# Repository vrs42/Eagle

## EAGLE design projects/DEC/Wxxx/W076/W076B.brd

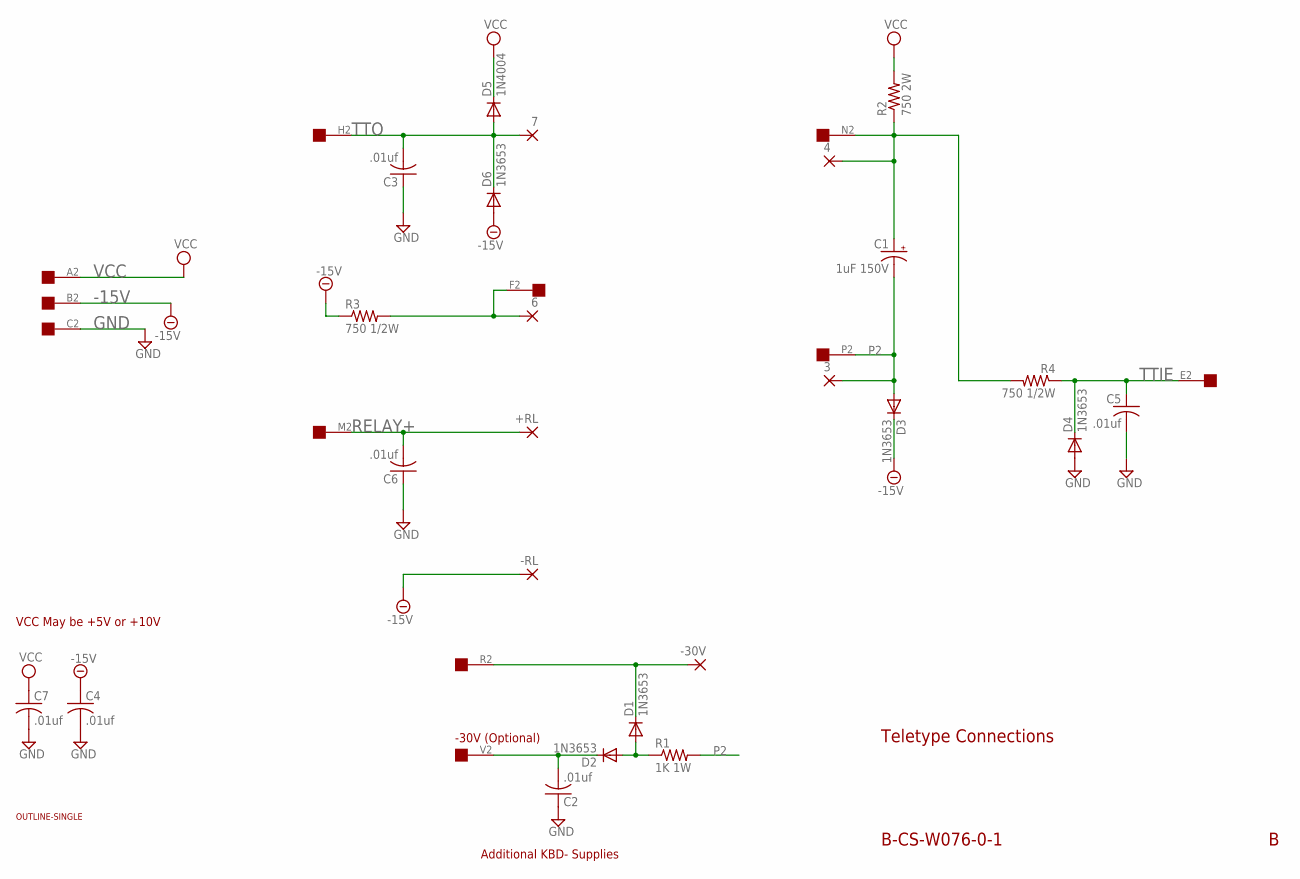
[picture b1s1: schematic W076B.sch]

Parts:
3, 4, 6, 7: 2,54/1,0
+RL: 2,54/1,0
-30V: 2,54/1,0
-RL: 2,54/1,0
C1: 1uF 150V; E25-9
C2, C3, C4, C5, C6, C7: .01uf; C050-025X075
D1, D2, D3, D4, D6: 1N3653; DO35-10
D5: 1N4004; DO35-10
EDGE: EDGE-1; EDGE-CON1
R1: 1K 1W; 0617/22
R2: 750 2W; P0817/22
R3, R4: 750 1/2W; 0411/15
U$1: OUTLINE-SINGLE; SINGLE

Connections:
-15V: -RL.1, C4.1, D3.C, D6.A, EDGE.B2, R3.1
GND: C2.1, C3.1, C4.2, C5.2, C6.1, C7.2, D4.A, EDGE.C2
unnamed: 6.1, EDGE.F2, R3.2
unnamed: -30V.1, D1.C, EDGE.R2
unnamed: C2.2, D2.C, EDGE.V2
unnamed: D1.A, D2.A, R1.1
unnamed: 4.1, C1.+, EDGE.N2, R2.1, R4.2
P2: 3.1, C1.-, D3.A, EDGE.P2, R1.2
RELAY+: +RL.1, C6.2, EDGE.M2
TTIE: C5.1, D4.C, EDGE.E2, R4.1
TTO: 7.1, C3.2, D5.A, D6.C, EDGE.H2
VCC: C7.1, D5.C, EDGE.A2, R2.2

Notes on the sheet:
Teletype Connections
VCC May be +5V or +10V
Additional KBD- Supplies
-30V (Optional)
B-CS-W076-0-1

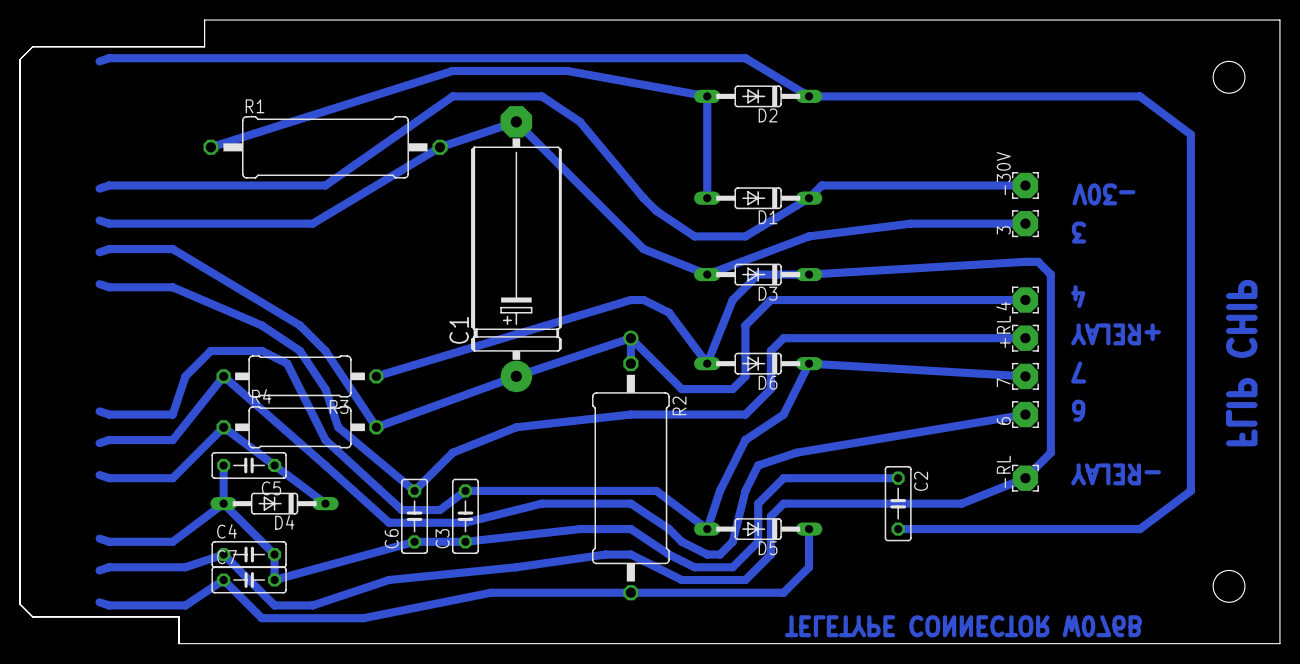
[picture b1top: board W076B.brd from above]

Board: 2 copper layers, 125.7 x 62.2 mm, 27 parts (1 on the bottom side), 12 nets.

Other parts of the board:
U$2: FLIPCHIP

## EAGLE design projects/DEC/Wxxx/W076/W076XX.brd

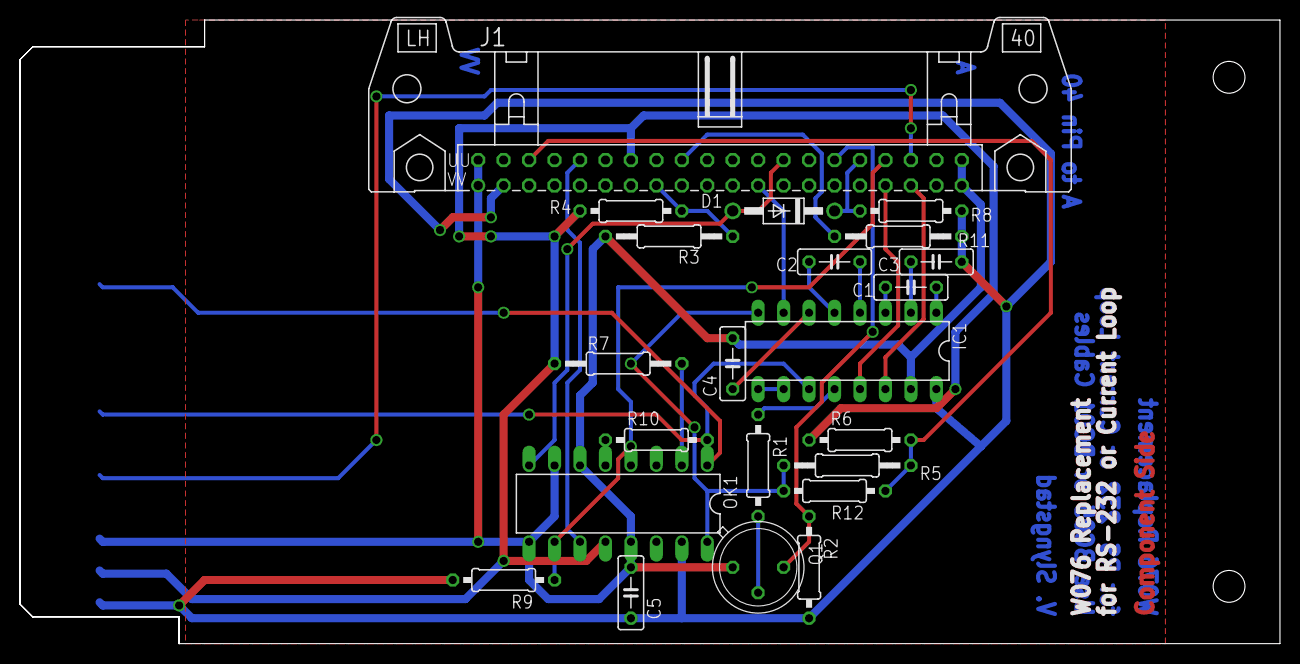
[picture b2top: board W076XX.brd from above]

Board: 2 copper layers, 125.7 x 62.2 mm, 24 parts (0 on the bottom side), 29 nets.

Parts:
C1, C2, C3, C4, C5: .1uf; C050-025X075
D1: 1N914; DO41-10
IC1: MAX232A; DIL16
J1: DEC40PINSH; DEC40PINH
OK1: LTV845; DIL16
Q1: PN2222; TO5
R1: 470; 0207/10
R2, R6, R9, R12: 5.1K; 0207/10
R3, R5, R7: 680 1/2W; 0207/12
R4, R8, R10: 220; 0207/10
R11: 1K 1/2W; 0207/12
U$2: EDGE-1; EDGE-CON1
U$3: OUTLINE-SINGLE; SINGLE

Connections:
20MA-INTERLOCK: J1.H, OK1.10, R9.1
+20MA: D1.C, J1.K, R8.1
-15V: J1.EE, OK1.12, R4.2, R6.1, R7.1, U$2.B2
-20MA: D1.A, J1.S, OK1.8
DTR-EIA: J1.DD, R3.1, R4.1
EIA-INTERLOCK: J1.M, Q1.3, R2.1
GND: C4.2, C5.1, IC1.15, J1.A, J1.B, J1.UU, J1.VV, OK1.6, OK1.7, OK1.9, OK1.13, Q1.1, R3.2, U$2.C2
unnamed: C2.1, IC1.5
unnamed: C2.2, IC1.4
unnamed: C1.2, IC1.1
unnamed: C1.1, IC1.3
unnamed: OK1.2, R7.2
unnamed: IC1.9, IC1.10
unnamed: IC1.8, OK1.16, R5.2, R12.2
unnamed: IC1.12, R1.1
unnamed: C3.2, IC1.2
unnamed: C4.1, IC1.6
unnamed: Q1.2, R1.2
unnamed: OK1.5, R10.1
RDR-RUN: OK1.1, U$2.M2
RELAY+: J1.PP, R5.1, R6.2, R12.1
RTS-EIA: IC1.7, J1.V
RX-DATA: J1.E, U$2.E2
RX-EIA: IC1.13, J1.J
TX+: J1.AA, R11.2
TX-: J1.KK, OK1.11
TX-DATA: IC1.11, R10.2, U$2.H2
TX-EIA: IC1.14, J1.F
VCC: C3.1, C5.2, IC1.16, J1.TT, OK1.15, R2.2, R8.2, R9.2, R11.1, U$2.A2

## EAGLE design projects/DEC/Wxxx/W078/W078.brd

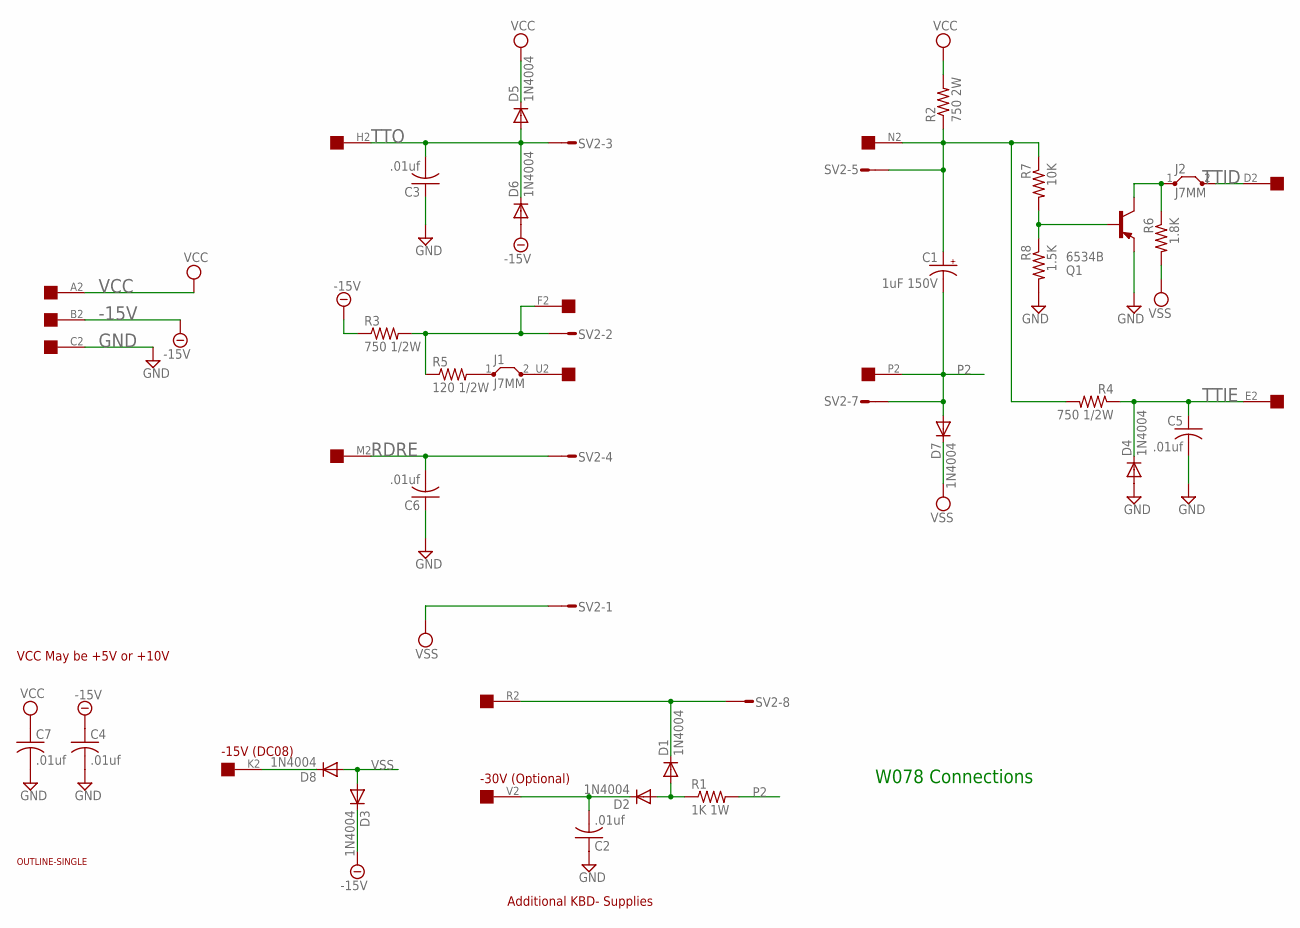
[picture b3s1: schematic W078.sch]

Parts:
C1: 1uF 150V; E22-6
C2, C3, C4, C5, C6, C7: .01uf; C050-025X075
D1, D2, D3, D4, D5, D6, D7, D8: 1N4004; DO35-10
EDGE: EDGE-1; EDGE-CON1
J1, J2: J7MM; 07
Q1: 6534B; TO92/
R1: 1K 1W; 0411/15
R2: 750 2W; 0411/15
R3, R4: 750 1/2W; 0309/12
R5: 120 1/2W; 0309/12
R6: 1.8K; 0207/10
R7: 10K; 0207/10
R8: 1.5K; 0207/10
SV2: L08P
U$1: OUTLINE-SINGLE; SINGLE

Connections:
-15V: C4.1, D3.C, D6.A, EDGE.B2, R3.1
GND: C2.1, C3.1, C4.2, C5.2, C6.1, C7.2, D4.A, EDGE.C2, Q1.1 (E), R8.2
unnamed: EDGE.F2, R3.2, R5.1, SV2.2
unnamed: Q1.2 (B), R7.2, R8.1
unnamed: D1.C, EDGE.R2, SV2.8
unnamed: D8.C, EDGE.K2
unnamed: C2.2, D2.C, EDGE.V2
unnamed: D1.A, D2.A, R1.1
unnamed: C1.+, EDGE.N2, R2.1, R4.2, R7.1, SV2.5
unnamed: J1.1, R5.2
unnamed: J2.1, Q1.3 (C), R6.1
P2: C1.-, D7.A, EDGE.P2, R1.2, SV2.7
RDRE: C6.2, EDGE.M2, SV2.4
TTID: EDGE.D2, J2.2
TTIE: C5.1, D4.C, EDGE.E2, R4.1
TTO: C3.2, D5.A, D6.C, EDGE.H2, SV2.3
TTOE: EDGE.U2, J1.2
VCC: C7.1, D5.C, EDGE.A2, R2.2
VSS: D3.A, D7.C, D8.A, R6.2, SV2.1

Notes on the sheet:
W078 Connections
VCC May be +5V or +10V
Additional KBD- Supplies
-30V (Optional)
-15V (DC08)

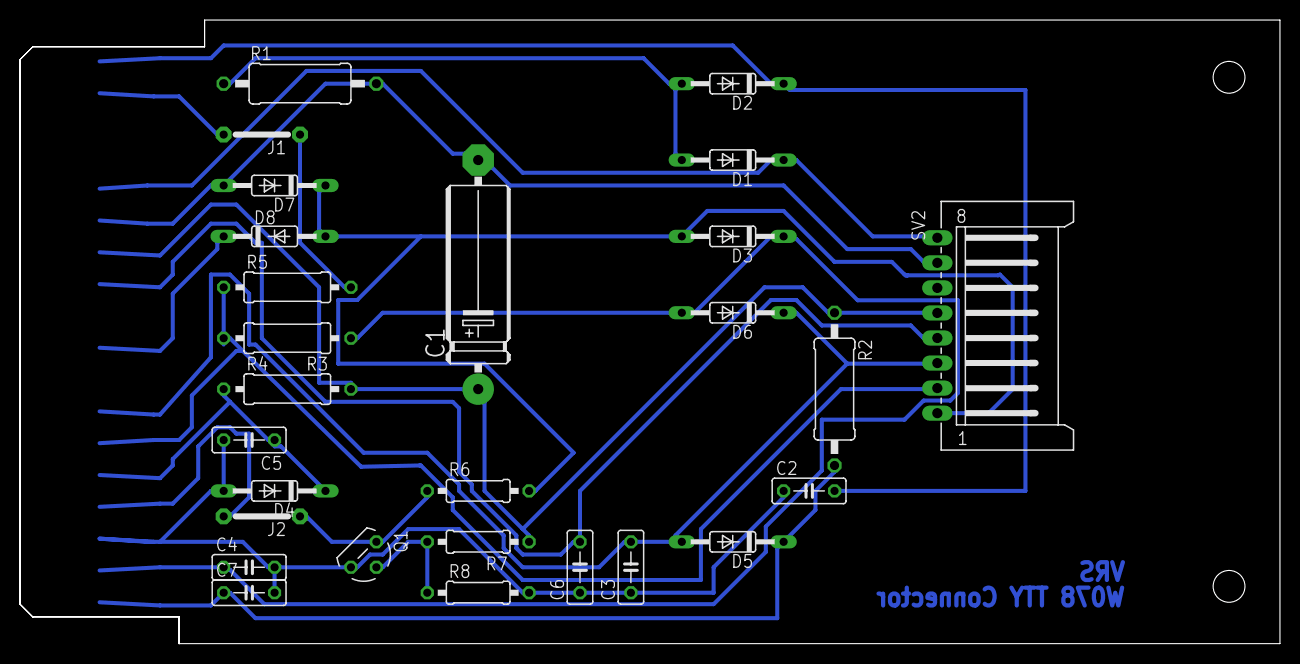
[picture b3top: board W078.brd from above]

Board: 2 copper layers, 125.7 x 62.2 mm, 29 parts (0 on the bottom side), 19 nets.

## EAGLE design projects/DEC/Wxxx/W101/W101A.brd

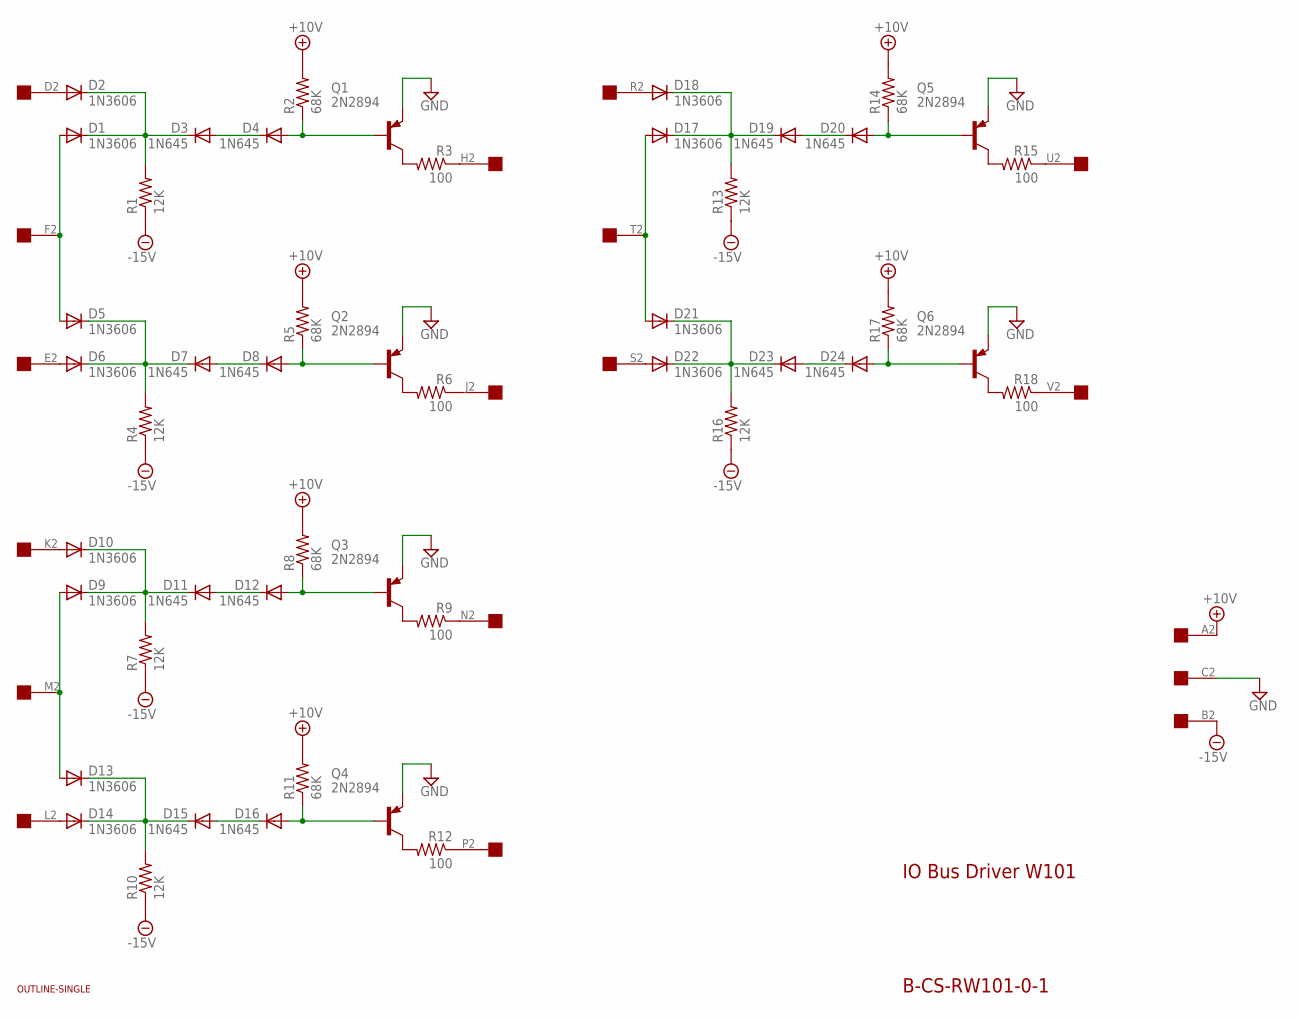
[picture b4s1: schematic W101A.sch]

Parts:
D1, D2, D5, D6, D9, D10, D13, D14, D17, D18, D21, D22: 1N3606; DO35-10
D3, D4, D7, D8, D11, D12, D15, D16, D19, D20, D23, D24: 1N645; DO35-10
Q1, Q2, Q3, Q4, Q5, Q6: 2N2894; TO39
R1, R4, R7, R10, R13, R16: 12K; 0207/10
R2, R5, R8, R11, R14, R17: 68K; 0207/10
R3, R6, R9, R12, R15, R18: 100; 0207/10
U$1: OUTLINE-SINGLE; SINGLE
U$2: EDGE-1; EDGE-CON1

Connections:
+10V: R2.2, R5.2, R8.2, R11.2, R14.2, R17.2, U$2.A2
-15V: R1.1, R4.1, R7.1, R10.1, R13.1, R16.1, U$2.B2
GND: Q1.1 (E), Q2.1 (E), Q3.1 (E), Q4.1 (E), Q5.1 (E), Q6.1 (E), U$2.C2
unnamed: D2.A, U$2.D2
unnamed: D8.A, Q2.2 (B), R5.1
unnamed: R3.1, U$2.H2
unnamed: Q2.3 (C), R6.2
unnamed: D6.A, U$2.E2
unnamed: D5.C, D6.C, D7.C, R4.2
unnamed: D7.A, D8.C
unnamed: D12.A, Q3.2 (B), R8.1
unnamed: Q3.3 (C), R9.2
unnamed: D9.A, D13.A, U$2.M2
unnamed: D9.C, D10.C, D11.C, R7.2
unnamed: D11.A, D12.C
unnamed: R6.1, U$2.J2
unnamed: D10.A, U$2.K2
unnamed: R9.1, U$2.N2
unnamed: R12.1, U$2.P2
unnamed: D18.A, U$2.R2
unnamed: R15.1, U$2.U2
unnamed: D4.A, Q1.2 (B), R2.1
unnamed: Q1.3 (C), R3.2
unnamed: D1.A, D5.A, U$2.F2
unnamed: D1.C, D2.C, D3.C, R1.2
unnamed: D3.A, D4.C
unnamed: D16.A, Q4.2 (B), R11.1
unnamed: Q4.3 (C), R12.2
unnamed: D14.A, U$2.L2
unnamed: D13.C, D14.C, D15.C, R10.2
unnamed: D15.A, D16.C
unnamed: D20.A, Q5.2 (B), R14.1
unnamed: Q5.3 (C), R15.2
unnamed: D17.A, D21.A, U$2.T2
unnamed: D17.C, D18.C, D19.C, R13.2
unnamed: D19.A, D20.C
unnamed: D24.A, Q6.2 (B), R17.1
unnamed: Q6.3 (C), R18.2
unnamed: D22.A, U$2.S2
unnamed: D21.C, D22.C, D23.C, R16.2
unnamed: D23.A, D24.C
unnamed: R18.1, U$2.V2

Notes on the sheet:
IO Bus Driver W101
B-CS-RW101-0-1

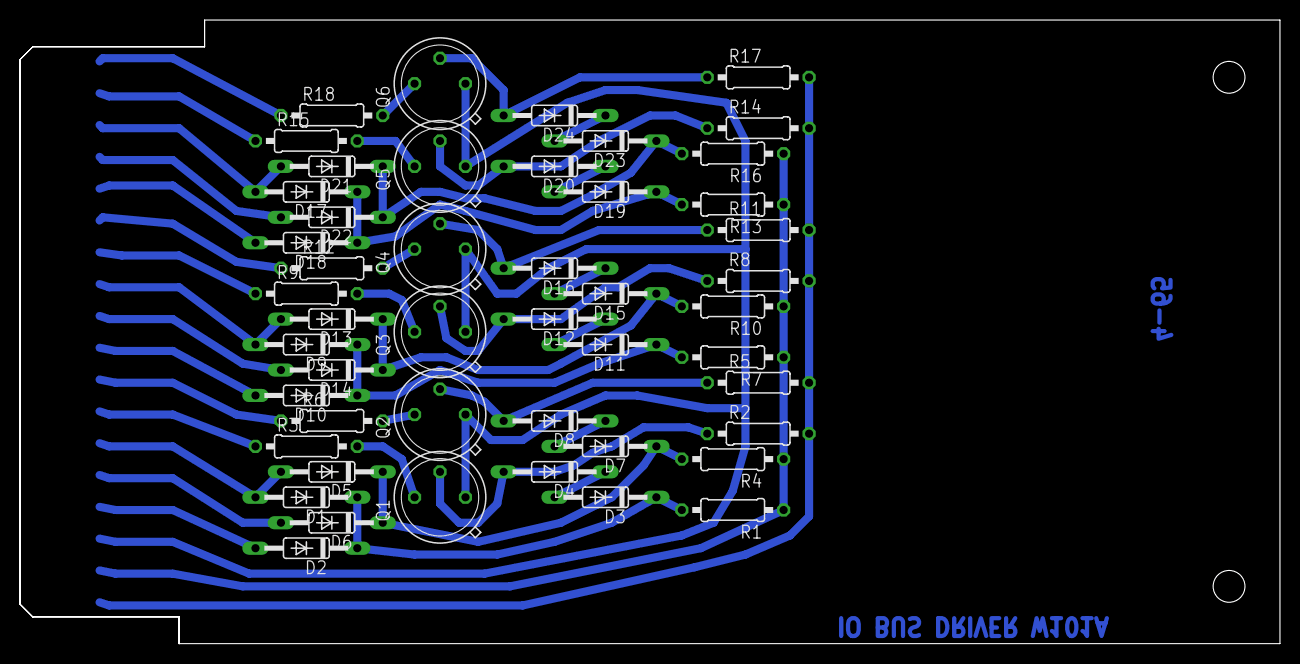
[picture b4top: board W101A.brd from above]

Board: 2 copper layers, 125.7 x 62.2 mm, 50 parts (0 on the bottom side), 42 nets.
